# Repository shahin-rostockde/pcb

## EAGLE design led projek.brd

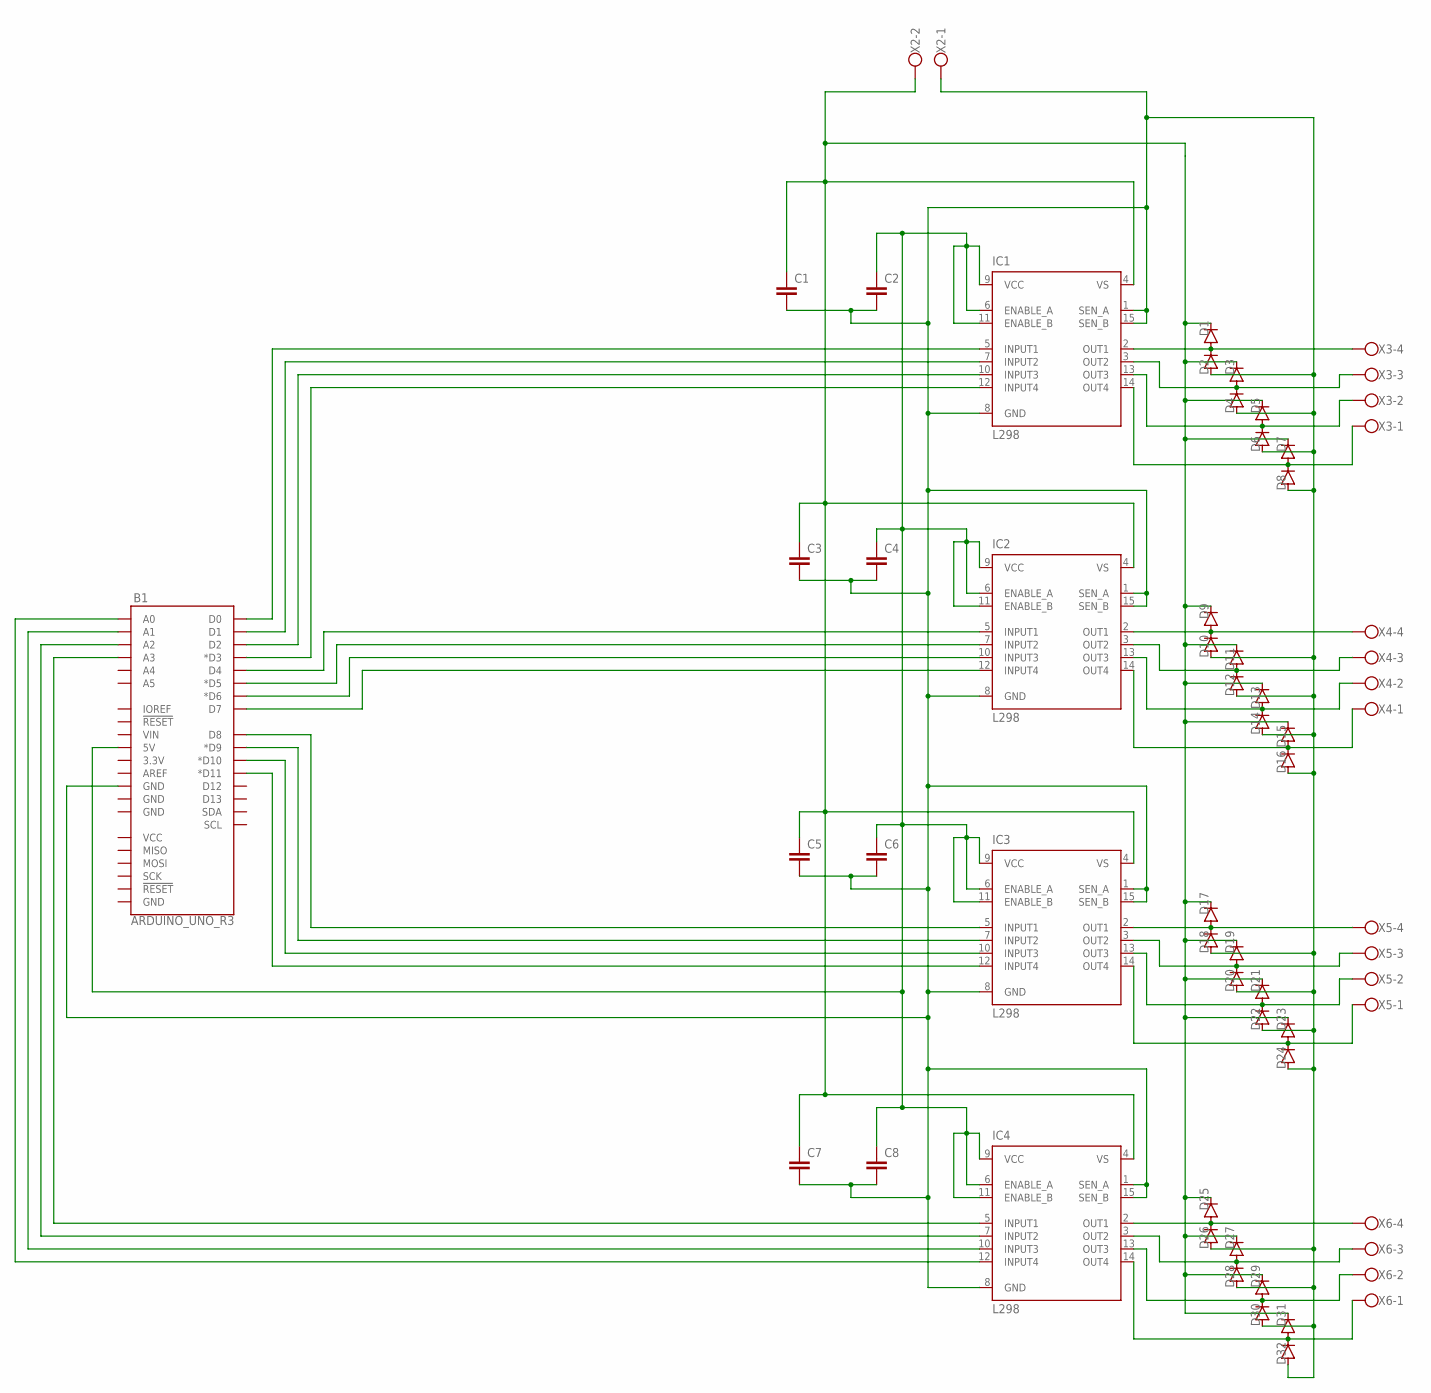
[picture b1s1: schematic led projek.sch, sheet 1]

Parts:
B1: ARDUINO_UNO_R3; ARDUINO_R3
C1, C2, C3, C4, C5, C6, C7, C8: C-EUC0805K; C0805K
D1, D2, D3, D4, D5, D6, D7, D8, D9, D10, D11, D12, D13, D14, D15, D16, D17, D18, D19, D20, D21, D22, D23, D24, D25, D26, D27, D28, D29, D30, D31, D32: DIODE-DO-214AC; DO-214AC
IC1, IC2, IC3, IC4: L298; MULTIWATT-15
X2: W237-102
X3, X4, X5, X6: W237-4

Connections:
unnamed: B1.D0, IC1.5 (INPUT1)
unnamed: B1.D1, IC1.7 (INPUT2)
unnamed: B1.D2, IC1.10 (INPUT3)
unnamed: B1.D3 (*D3), IC1.12 (INPUT4)
unnamed: B1.D4, IC2.5 (INPUT1)
unnamed: B1.D5 (*D5), IC2.7 (INPUT2)
unnamed: B1.D6 (*D6), IC2.10 (INPUT3)
unnamed: B1.D7, IC2.12 (INPUT4)
unnamed: B1.D8, IC3.5 (INPUT1)
unnamed: B1.D9 (*D9), IC3.7 (INPUT2)
unnamed: B1.D10 (*D10), IC3.10 (INPUT3)
unnamed: B1.D11 (*D11), IC3.12 (INPUT4)
unnamed: B1.A0, IC4.12 (INPUT4)
unnamed: B1.A1, IC4.10 (INPUT3)
unnamed: B1.A2, IC4.7 (INPUT2)
unnamed: B1.A3, IC4.5 (INPUT1)
unnamed: D3.A, D4.C, IC1.3 (OUT2), X3.3
unnamed: D11.A, D12.C, IC2.3 (OUT2), X4.3
unnamed: D5.A, D6.C, IC1.13 (OUT3), X3.2
unnamed: D7.A, D8.C, IC1.14 (OUT4), X3.1
unnamed: D9.A, D10.C, IC2.2 (OUT1), X4.4
unnamed: D13.A, D14.C, IC2.13 (OUT3), X4.2
unnamed: D15.A, D16.C, IC2.14 (OUT4), X4.1
unnamed: B1.GND@4 (GND), C1.2, C2.2, C3.2, C4.2, C5.2, C6.2, C7.2, C8.2, D2.A, D4.A, D6.A, D8.A, D10.A, D12.A, D14.A, D16.A, D18.A, D20.A, D22.A, D24.A, D26.A, D28.A, D30.A, D32.A, IC1.1 (SEN_A), IC1.8 (GND), IC1.15 (SEN_B), IC2.1 (SEN_A), IC2.8 (GND), IC2.15 (SEN_B), IC3.1 (SEN_A), IC3.8 (GND), IC3.15 (SEN_B), IC4.1 (SEN_A), IC4.8 (GND), IC4.15 (SEN_B), X2.1
unnamed: D25.A, D26.C, IC4.2 (OUT1), X6.4
unnamed: D27.A, D28.C, IC4.3 (OUT2), X6.3
unnamed: D29.A, D30.C, IC4.13 (OUT3), X6.2
unnamed: D17.A, D18.C, IC3.2 (OUT1), X5.4
unnamed: D19.A, D20.C, IC3.3 (OUT2), X5.3
unnamed: D21.A, D22.C, IC3.13 (OUT3), X5.2
unnamed: D31.A, D32.C, IC4.14 (OUT4), X6.1
unnamed: D23.A, D24.C, IC3.14 (OUT4), X5.1
unnamed: C1.1, C3.1, C5.1, C7.1, D1.C, D3.C, D5.C, D7.C, D9.C, D11.C, D13.C, D15.C, D17.C, D19.C, D21.C, D23.C, D25.C, D27.C, D29.C, D31.C, IC1.4 (VS), IC2.4 (VS), IC3.4 (VS), IC4.4 (VS), X2.2
unnamed: D1.A, D2.C, IC1.2 (OUT1), X3.4
unnamed: B1.5V, C2.1, C4.1, C6.1, C8.1, IC1.6 (ENABLE_A), IC1.9 (VCC), IC1.11 (ENABLE_B), IC2.6 (ENABLE_A), IC2.9 (VCC), IC2.11 (ENABLE_B), IC3.6 (ENABLE_A), IC3.9 (VCC), IC3.11 (ENABLE_B), IC4.6 (ENABLE_A), IC4.9 (VCC), IC4.11 (ENABLE_B)

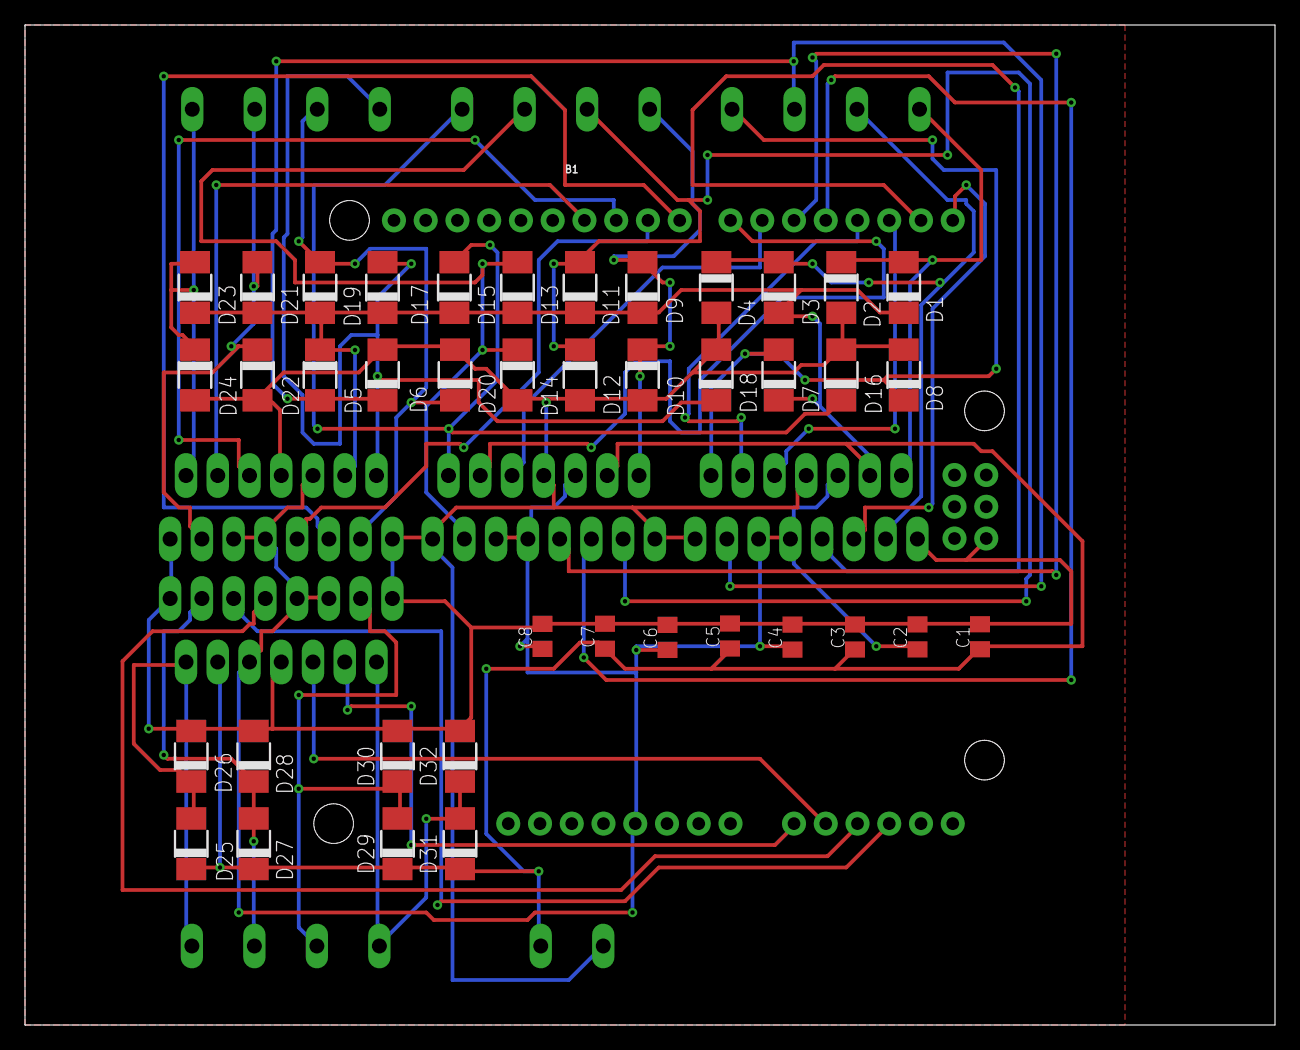
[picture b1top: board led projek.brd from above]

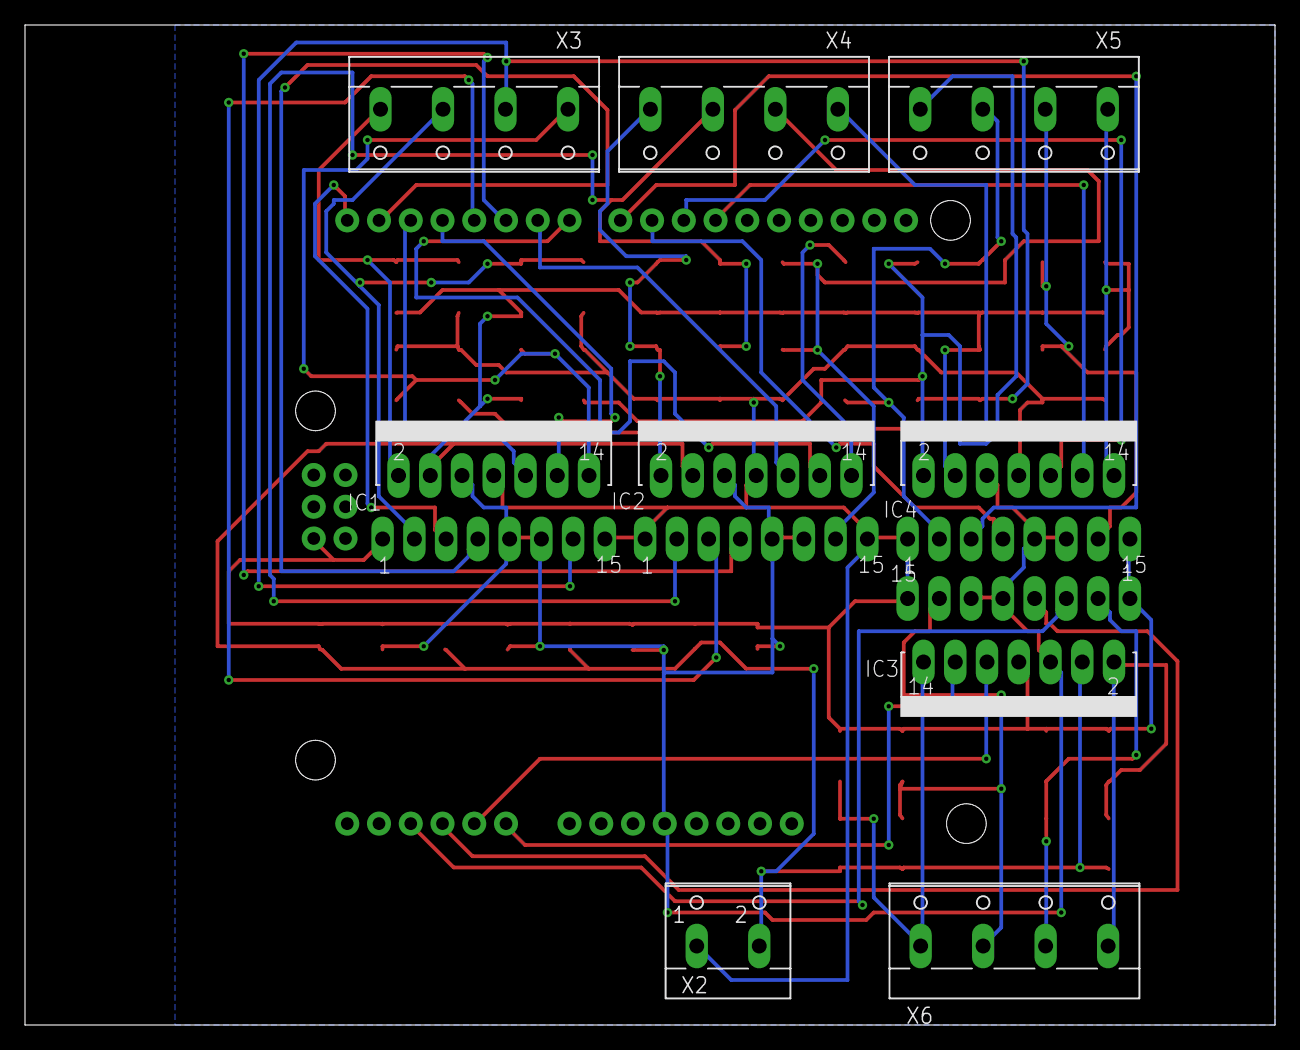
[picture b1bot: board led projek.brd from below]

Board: 2 copper layers, 100.0 x 80.0 mm, 50 parts (9 on the bottom side), 35 nets.

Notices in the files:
parts and their libraries:
SparkFun-Boards: Licensing: Creative Commons ShareAlike 4.0 International - https://creativecommons.org/licenses/by-sa/4.0
